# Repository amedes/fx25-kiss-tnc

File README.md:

# FX.25 KISS TNC

KISS TNC program supporing FX.25 error correction protocol.

Hardware components
* TCM3105
* ESP32-WROOM-32

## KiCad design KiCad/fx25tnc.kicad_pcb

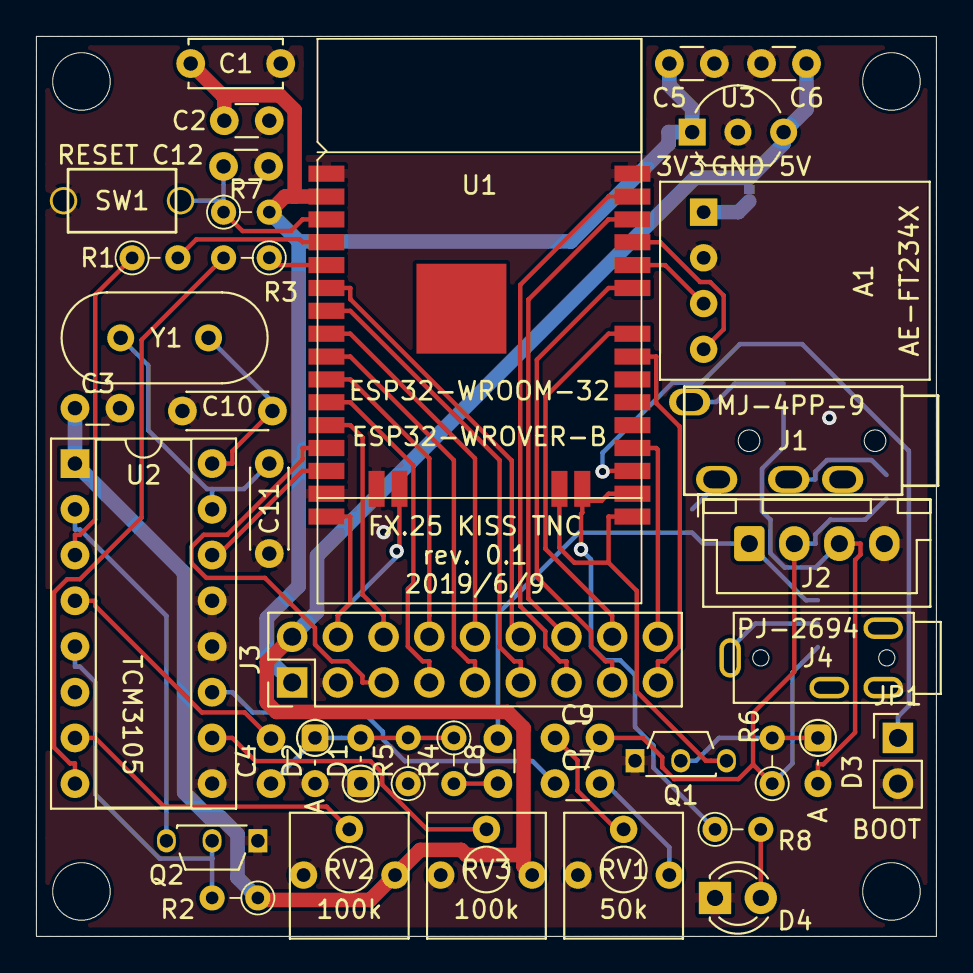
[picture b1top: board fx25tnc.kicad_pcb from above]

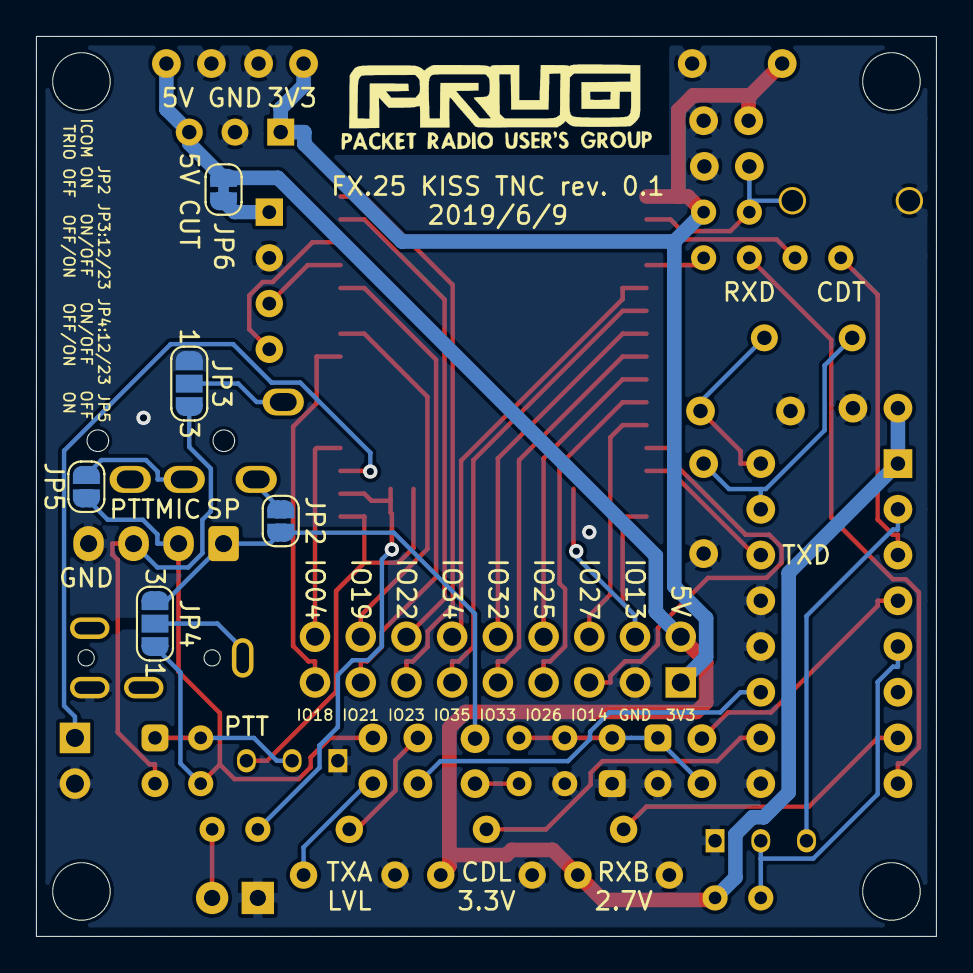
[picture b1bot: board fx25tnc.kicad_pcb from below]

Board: 2 copper layers, 50.0 x 50.0 mm, 49 parts (5 on the bottom side), 51 nets.

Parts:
A1: AE-FT234X
C1: 10u; C_Disc_D5.0mm_W2.5mm_P5.00mm
C2, C4, C6, C7, C8, C9, C12: 0.1u; C_Disc_D3.0mm_W1.6mm_P2.50mm
C3, C5: 1u; C_Disc_D3.0mm_W1.6mm_P2.50mm
C10, C11: 33p; C_Disc_D4.3mm_W1.9mm_P5.00mm
D1, D2, D3: 1SS178; D_DO-34_SOD68_P2.54mm_Vertical_AnodeUp
D4: CDT; LED_D3.0mm
J1: MJ-4PP-9
J2: Conn_01x04; JST_XH_B4B-XH-A_1x04_P2.50mm_Vertical
J3: Conn_02x09_Odd_Even; PinHeader_2x09_P2.54mm_Vertical
J4: PJ-2694; Jack_2.5mm_PJ2964
JP1: BOOT; PinHeader_1x02_P2.54mm_Vertical
JP2, JP5: SolderJumper_2_Open; SolderJumper-2_P1.3mm_Open_RoundedPad1.0x1.5mm
JP3, JP4: SolderJumper_3_Open; SolderJumper-3_P1.3mm_Open_RoundedPad1.0x1.5mm_NumberLabels
JP6: SolderJumper_2_Bridged; SolderJumper-2_P1.3mm_Bridged_RoundedPad1.0x1.5mm
MH1, MH2, MH3, MH4: MountingHole_3.2mm_M3
Q1, Q2: DTC143EL; TO-92S_Wide
R1, R3, R4, R5, R6, R7: 10k; R_Axial_DIN0204_L3.6mm_D1.6mm_P2.54mm_Vertical
R2: 100k; R_Axial_DIN0204_L3.6mm_D1.6mm_P2.54mm_Vertical
R8: 1k; R_Axial_DIN0204_L3.6mm_D1.6mm_P2.54mm_Vertical
RV1: 50k; BOURNS_362P
RV2, RV3: 100k; BOURNS_362P
SW1: RESET; TACTSW_6x3.5mm_TH
U1: ESP32-WROOM-32; ESP32-WROVER
U2: TCM3105; DIP-16_W7.62mm_Socket
U3: LP2950-3.3_TO92; TO-92_Inline_Wide
Y1: 4.4336MHz; Crystal_HC49-4H_Vertical

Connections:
+3V3: C1.1, C2.1, C5.1, J3.1, R7.2, U1.2, U3.1
+5V: C3.1, C6.1, J3.2, JP6.1, R2.1, RV2.3, RV3.3, U2.1, U3.3
/MIC: C9.1, J2.2, JP4.1, JP5.1, R6.1
/PTT: D3.2, J2.3, JP3.3
/SP: C8.2, J2.1, JP2.1, JP4.3
CDT: R1.1, U2.3
GND: A1.2, C1.2, C2.2, C3.2, C5.2, C6.2, C10.1, C11.1, C12.1, D1.1, D2.2, D4.1, J2.4, J3.3, J4.1, JP1.2, JP3.1, Q1.1, Q2.1, R5.1, RV1.1, RV2.1, RV3.1, SW1.1, U1.1, U1.15, U1.38, U2.9, U2.12, U2.13, U3.2
IO4: J3.18, U1.26
IO13: J3.4, U1.16
IO14: J3.5, U1.13
IO18: J3.17, U1.30
IO19: J3.16, U1.31
IO21: J3.15, U1.33
IO22: J3.14, U1.36
IO23: J3.13, U1.37
IO25: J3.8, U1.10
IO26: J3.7, U1.11
IO27: J3.6, U1.12
IO32: J3.10, U1.8
IO33: J3.9, U1.9
IO34: J3.12, U1.6
IO35: J3.11, U1.7
LED: R8.1, U1.24
unnamed: A1.1, JP6.2
unnamed: C4.1, D1.2, D2.1, R4.1, R5.2
unnamed: C4.2, U2.4
unnamed: C7.1, RV1.3
unnamed: C7.2, U2.11
unnamed: C8.1, R4.2
unnamed: C9.2, RV1.2
unnamed: C10.2, U2.16, Y1.1
unnamed: C11.2, U2.15, Y1.2
unnamed: C12.2, R7.1, SW1.2, U1.3
unnamed: D3.1, Q1.2, R6.2
unnamed: D4.2, R8.2
unnamed: J1.1, JP3.2
unnamed: J1.3, JP5.2
unnamed: J1.4, JP2.2
unnamed: J4.2, JP4.2
unnamed: JP1.1, U1.25
unnamed: Q2.2, R2.2, U2.5
unnamed: Q2.3, U2.2
unnamed: R1.2, U1.4
unnamed: R3.1, U1.5
unnamed: RV2.2, U2.7
unnamed: RV3.2, U2.10
PTT0: Q1.3, U1.23
RXD: R3.2, U2.8
RXD0: A1.3, U1.34
TXD: U1.14, U2.14
TXD0: A1.4, U1.35

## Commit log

2019-07-01 fix TNC_PORT undefined
2019-07-01 add KiCad files and manual
2019-07-13 add writing firmware section
2019-07-19 correct wrong include file rmt.c to rmt.h
2019-07-19 add cmake support files
2019-07-19 add how to write firmware using idf.py
2019-07-19 add switch SW1 to parts list
2019-07-23 update the manual to use ESP-IDF stable(v3.2.2)
2019-08-04 fixed src address of beacon packet
2019-08-17 add TNC demo mode
2019-08-18 use rand_r() to prevent interferance between threads
2019-08-18 set 0x7e at first FX.25 frame byte before RS decode
2019-08-18 randomize demo beacon transmitting interval
2019-08-18 fix display of error correction in demo mode
2019-08-19 fix AX.25 start flag overwriting error correction
2019-08-19 rewrite KISS parameter setting
2019-08-20 rewrite p-persistent implimentation
2019-08-20 modify display of decode rate info
2019-08-20 tuning demo mode beacon interval
2019-08-20 add sequence number to demo mode beacon packet
2019-08-20 add display of Tag error in DEMO MODE
2019-08-20 add display of Reed Solomon decode error in DEMO MODE
2019-08-20 modify burst error in DEMO MODE
2019-08-20 modify output of Stat info in DEMO MODE
2019-08-21 add FX.25 FCS error count in DEMO MODE
2019-08-21 modify Tag error count from 12 to 13
2019-08-21 modify Tag error count from 13 to 11
2019-08-21 modify Tag error count from 11 to 12 in DEMO MODE
2019-08-22 add error value in RS decode error message
2019-08-26 use esp_random() instead of rand_r() to adding noise in DEMO MODE
2019-08-26 output number of bit errors in Tag
2019-08-26 modify output of Tag error in DEMO MODE
2019-08-27 allow multiple tcp connection
2019-08-27 fix Tag error bit output
2019-08-28 add SoftAP feature in DEMO MODE
2019-09-28 update manual
2019-09-28 update manual, add R7,SW1,C12,C1,C2
2019-12-13 add FX.25 packet information output option
2020-01-12 fixed ledc_init undefined error
2020-06-18 add ESP-IDF v4.x support
2020-06-18 improve RXD capture processing
2020-06-20 modify baud rate processing to enable other than 1200bps
2020-06-21 fix strncat string length error
2020-06-21 modify from xTaskCreate to xTaskCreatePinnedToCore
2020-06-26 fixed wrong result of poly_div() if quotient is zero
2020-06-26 fixed the incompatibility problem with Direwolf's FX.25 packet
2020-06-30 improve bit_count() performance
2020-07-30 add 2nd PNtag
2020-08-01 ESPLOG long long formatter
2020-08-07 Indentation Style Format
2020-08-12 Indentation Style Format2
2020-08-12 Separate Framesync
2020-08-14 choise_encode_info
2020-08-18 fix buffer size
2020-08-19 choise_decode_info
2020-08-23 buffer_info
2020-10-07 bitsync_info isolate
2020-10-07 output set
2020-10-07 split edge_level bit_level
2020-11-25 20201125save
2021-01-01 fixed the imcompatibility of shotened RS code with Direwolf
2021-01-03 improved AX.25 decode
2021-04-22 fixed wrong filename freertos/FreeRTOS.h
